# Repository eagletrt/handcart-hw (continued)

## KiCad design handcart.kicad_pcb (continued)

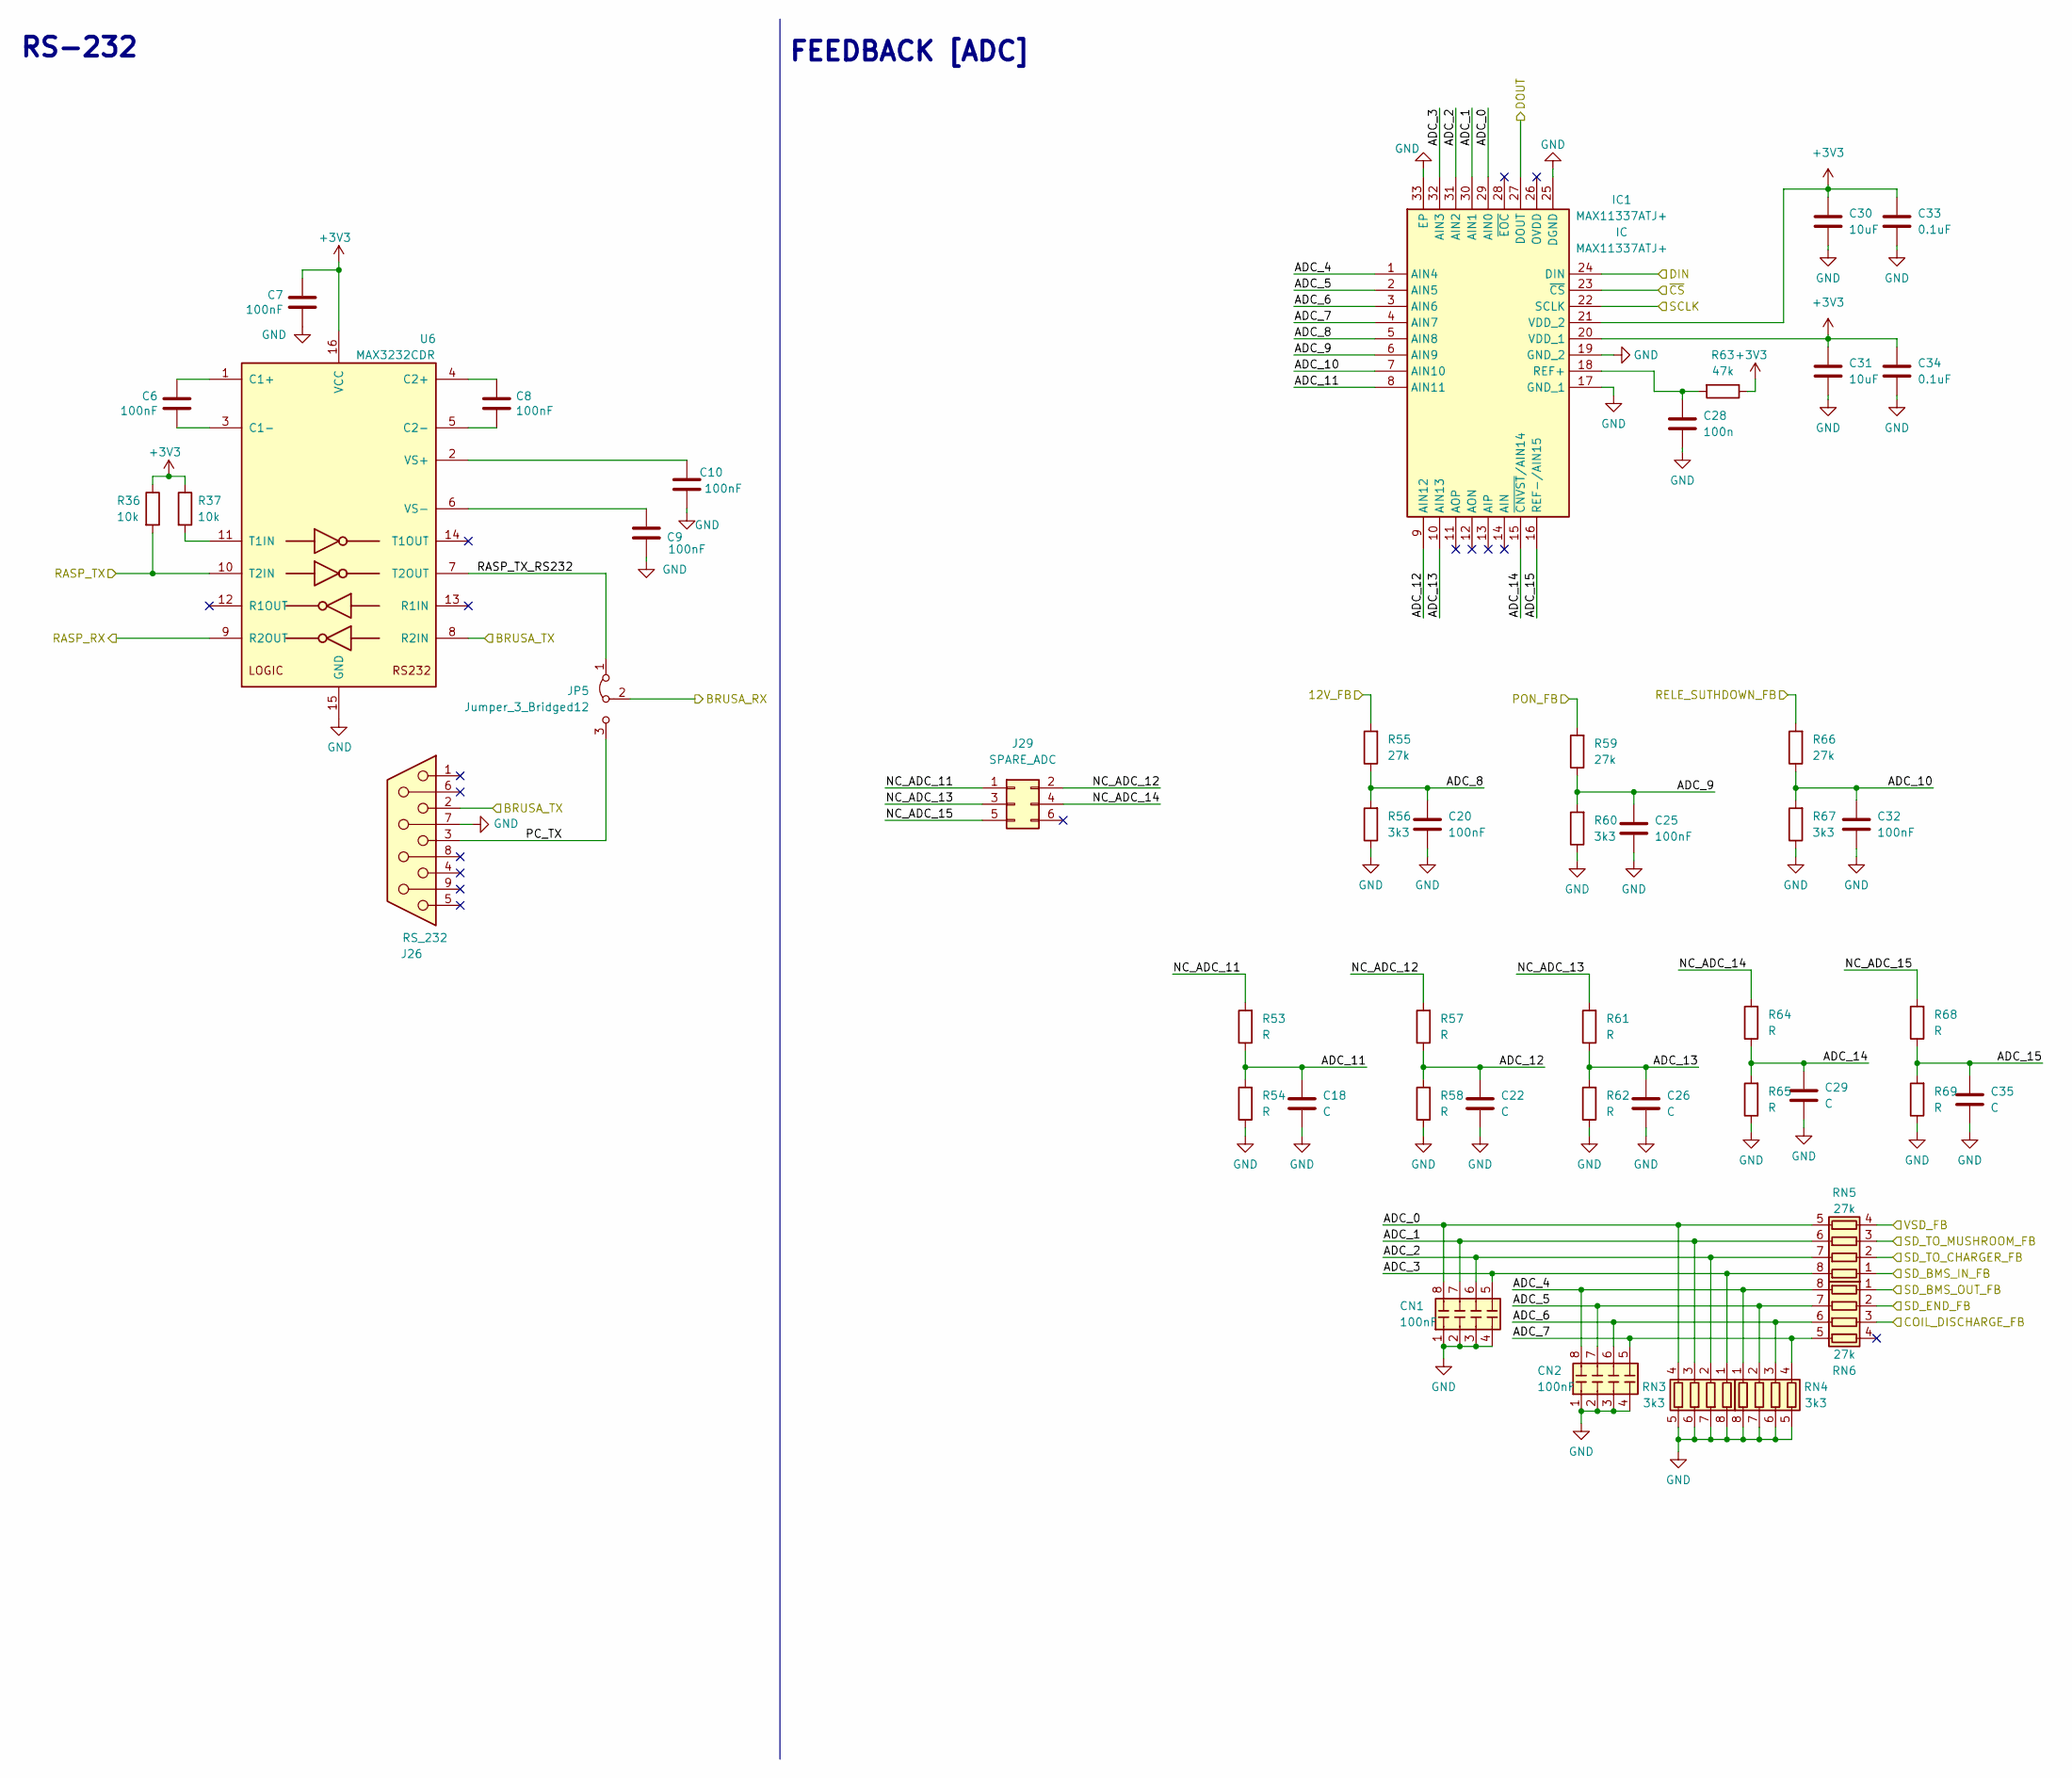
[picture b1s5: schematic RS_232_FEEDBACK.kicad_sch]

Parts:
C6, C7, C8, C9, C10, C20, C25, C32: 100nF; R_0603_1608Metric
C18, C22, C26, C29, C35: C; R_0805_2012Metric
C28: 100n; R_0603_1608Metric
C30, C31: 10uF; R_0603_1608Metric
C33, C34: 0.1uF; R_0603_1608Metric
CN1, CN2: 100nF; R_Array_Concave_4x0603; Mouser 581-W3A4YC104KAT2A
IC1: MAX11337ATJ+; QFN50P500X500X80-33N; Mouser Part Number 700-MAX11337ATJ+
J26: RS_232; DSUB-9_Female_Horizontal_P2.77x2.84mm_EdgePinOffset7.70mm_H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
J29: SPARE_ADC; Molex_Micro-Fit_3.0_43045-0612_2x03_P3.00mm_Vertical
JP5: Jumper_3_Bridged12; PinHeader_1x03_P2.54mm_Vertical
R36, R37: 10k; R_0603_1608Metric
R53, R54, R57, R58, R61, R62, R64, R65, R68, R69: R; R_0805_2012Metric
R55, R59, R66: 27k; R_0603_1608Metric
R56, R60, R67: 3k3; R_0603_1608Metric
R63: 47k; R_0603_1608Metric
RN3, RN4: 3k3; R_Array_Convex_4x0603
RN5, RN6: 27k; R_Array_Convex_4x0603
U6: MAX3232CDR; SOIC-16_3.9x9.9mm_P1.27mm

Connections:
+3V3: C7.1, C30.1, C31.1, C33.1, C34.1, IC1.20 (VDD_1), IC1.21 (VDD_2), R36.1, R37.1, R63.1, U6.16 (VCC); also elsewhere on the board
+12V: R55.2; also elsewhere on the board
/BRUSA_RX: JP5.2 (C); also elsewhere on the board
/BRUSA_TX: J26.2, U6.8 (R2IN); also elsewhere on the board
/PON: R59.2; also elsewhere on the board
/RS_232+FEEDBACK/ADC_0: CN1.8 (R1.2), IC1.29 (AIN0), RN3.4 (R4.1), RN5.5 (R4.2)
/RS_232+FEEDBACK/ADC_1: CN1.7 (R2.2), IC1.30 (AIN1), RN3.3 (R3.1), RN5.6 (R3.2)
/RS_232+FEEDBACK/ADC_2: CN1.6 (R3.2), IC1.31 (AIN2), RN3.2 (R2.1), RN5.7 (R2.2)
/RS_232+FEEDBACK/ADC_3: CN1.5 (R4.2), IC1.32 (AIN3), RN3.1 (R1.1), RN5.8 (R1.2)
/RS_232+FEEDBACK/ADC_4: CN2.8 (R1.2), IC1.1 (AIN4), RN4.1 (R1.1), RN6.8 (R1.2)
/RS_232+FEEDBACK/ADC_5: CN2.7 (R2.2), IC1.2 (AIN5), RN4.2 (R2.1), RN6.7 (R2.2)
/RS_232+FEEDBACK/ADC_6: CN2.6 (R3.2), IC1.3 (AIN6), RN4.3 (R3.1), RN6.6 (R3.2)
/RS_232+FEEDBACK/ADC_7: CN2.5 (R4.2), IC1.4 (AIN7), RN4.4 (R4.1), RN6.5 (R4.2)
/RS_232+FEEDBACK/ADC_8: C20.1, IC1.5 (AIN8), R55.1, R56.2
/RS_232+FEEDBACK/ADC_9: C25.1, IC1.6 (AIN9), R59.1, R60.2
/RS_232+FEEDBACK/ADC_10: C32.1, IC1.7 (AIN10), R66.1, R67.2
/RS_232+FEEDBACK/ADC_11: C18.1, IC1.8 (AIN11), R53.1, R54.2
/RS_232+FEEDBACK/ADC_12: C22.1, IC1.9 (AIN12), R57.1, R58.2
/RS_232+FEEDBACK/ADC_13: C26.1, IC1.10 (AIN13), R61.1, R62.2
/RS_232+FEEDBACK/ADC_14: C29.1, IC1.15 (~CNVST/AIN14), R64.1, R65.2
/RS_232+FEEDBACK/ADC_15: C35.1, IC1.16 (REF-/AIN15), R68.1, R69.2
/RS_232+FEEDBACK/COIL_DISCHARGE_FB: RN6.3 (R3.1); also elsewhere on the board
/RS_232+FEEDBACK/NC_ADC_11: J29.1, R53.2
/RS_232+FEEDBACK/NC_ADC_12: J29.2, R57.2
/RS_232+FEEDBACK/NC_ADC_13: J29.3, R61.2
/RS_232+FEEDBACK/NC_ADC_14: J29.4, R64.2
/RS_232+FEEDBACK/NC_ADC_15: J29.5, R68.2
/RS_232+FEEDBACK/PC_TX: J26.3, JP5.3 (B)
/RS_232+FEEDBACK/RASP_RX: U6.9 (R2OUT); also elsewhere on the board
/RS_232+FEEDBACK/RASP_TX: R36.2, U6.10 (T2IN); also elsewhere on the board
/RS_232+FEEDBACK/RASP_TX_RS232: JP5.1 (A), U6.7 (T2OUT)
/RS_232+FEEDBACK/RELE_SUTHDOWN_FB: R66.2; also elsewhere on the board
/RS_232+FEEDBACK/~CS: IC1.23 (~CS); also elsewhere on the board
/Raspberry/RASP_CLK: IC1.22 (SCLK); also elsewhere on the board
/Raspberry/RASP_MISO: IC1.27 (DOUT); also elsewhere on the board
/Raspberry/RASP_MOSI: IC1.24 (DIN); also elsewhere on the board
/SD_BMS_IN: RN5.1 (R1.1); also elsewhere on the board
/SD_BMS_OUT: RN6.1 (R1.1); also elsewhere on the board
/SD_END: RN6.2 (R2.1); also elsewhere on the board
/SD_TO_CHARGER: RN5.2 (R2.1); also elsewhere on the board
/SD_TO_MUSHROOM: RN5.3 (R3.1); also elsewhere on the board
GND: C7.2, C9.2, C10.2, C18.2, C20.2, C22.2, C25.2, C26.2, C28.2, C29.2, C30.2, C31.2, C32.2, C33.2, C34.2, C35.2, CN1.1 (R1.1), CN1.2 (R2.1), CN1.3 (R3.1), CN1.4 (R4.1), CN2.1 (R1.1), CN2.2 (R2.1), CN2.3 (R3.1), CN2.4 (R4.1), IC1.17 (GND_1), IC1.19 (GND_2), IC1.25 (DGND), IC1.33 (EP), J26.7, R54.1, R56.1, R58.1, R60.1, R62.1, R65.1, R67.1, R69.1, RN3.5 (R4.2), RN3.6 (R3.2), RN3.7 (R2.2), RN3.8 (R1.2), RN4.5 (R4.2), RN4.6 (R3.2), RN4.7 (R2.2), RN4.8 (R1.2), U6.15 (GND); also elsewhere on the board
unnamed: C6.1, U6.1 (C1+)
unnamed: C6.2, U6.3 (C1-)
unnamed: C8.1, U6.4 (C2+)
unnamed: C8.2, U6.5 (C2-)
unnamed: C9.1, U6.6 (VS-)
unnamed: C10.1, U6.2 (VS+)
unnamed: C28.1, IC1.18 (REF+), R63.2
unnamed: R37.2, U6.11 (T1IN)
VCC: RN5.4 (R4.1); also elsewhere on the board

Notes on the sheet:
RS-232
FEEDBACK [ADC]

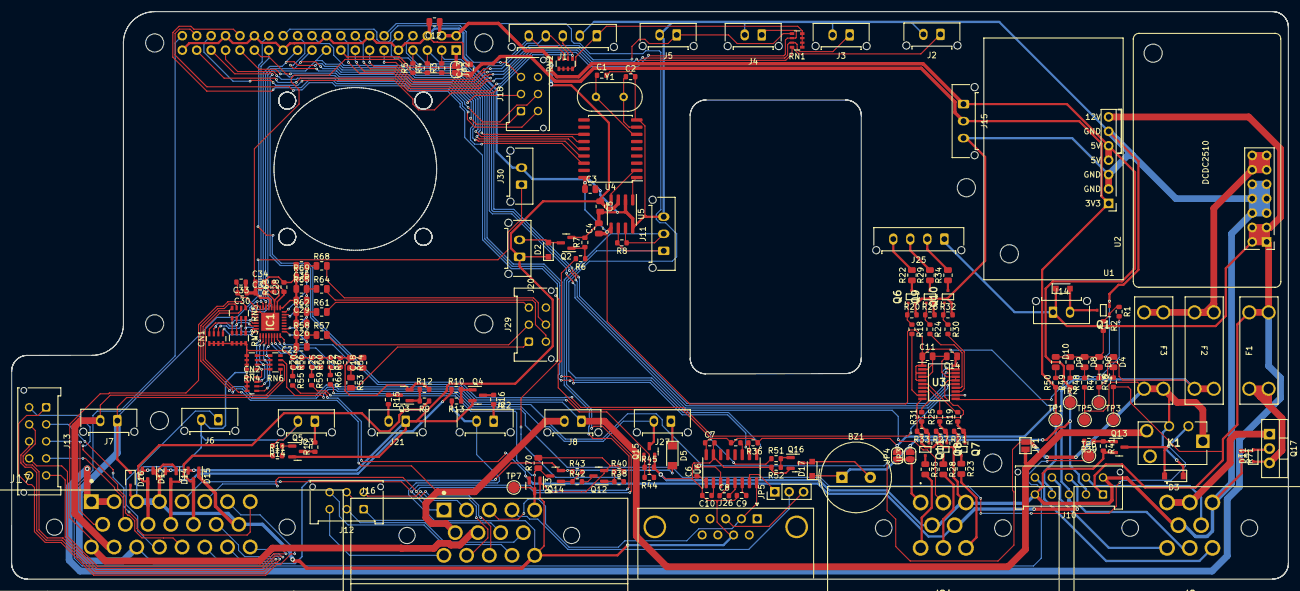
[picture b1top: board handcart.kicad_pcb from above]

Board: 2 copper layers, 225.0 x 100.0 mm, 193 parts (1 on the bottom side), 163 nets.

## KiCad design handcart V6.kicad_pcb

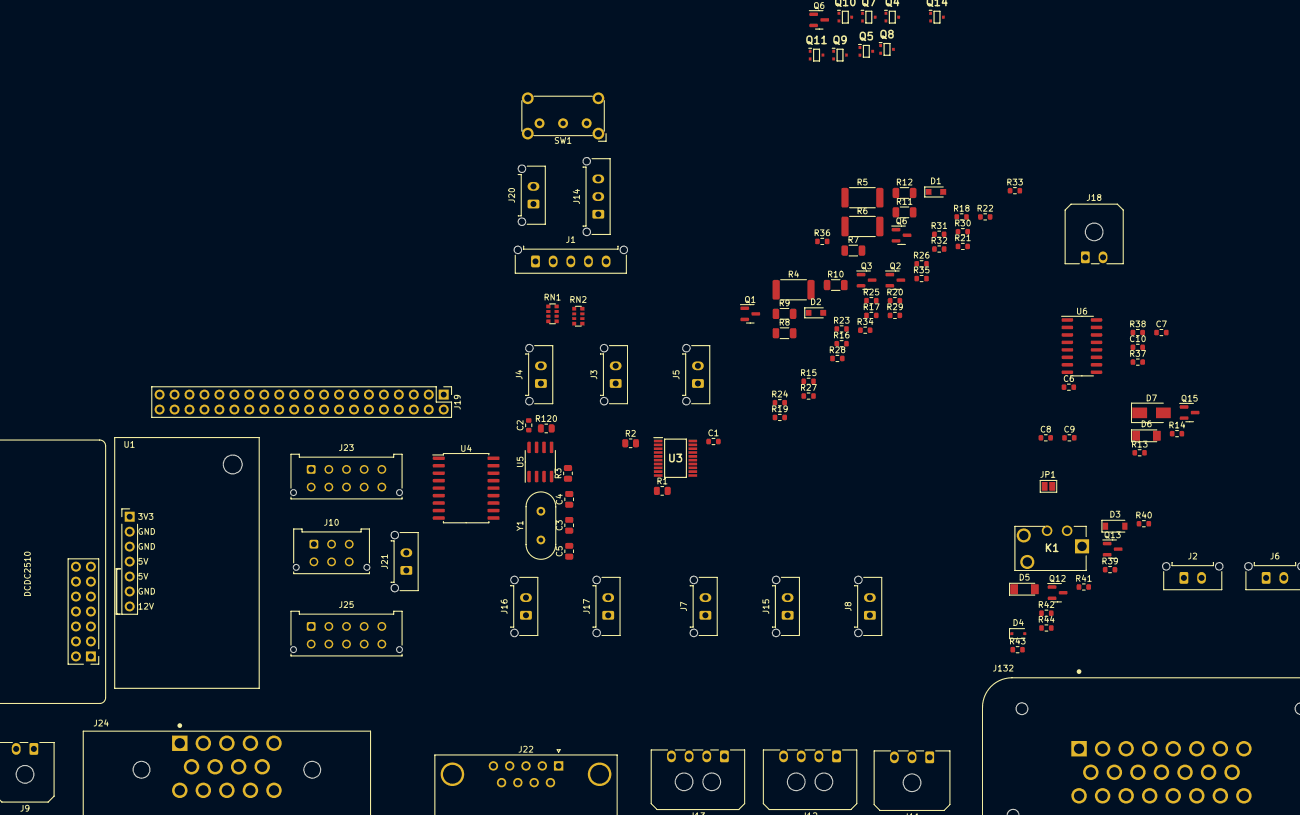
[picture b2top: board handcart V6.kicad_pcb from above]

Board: 2 copper layers, 116 parts (0 on the bottom side), 121 nets, no tracks yet.

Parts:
C1, C2: 18pF; R_0603_1608Metric
C3, C4, C5: 100nF; R_0805_2012Metric
C6, C7, C8, C9, C10: 100nF; R_0603_1608Metric
D1, D2: 1N4148W; D_SOD-323_HandSoldering
D3: 1N4148W; D_SOD-123
D4: DDZ13ASF 13V; D_SOD-323F
D5, D6: RGL34B; D_MiniMELF
D7: SMAJ40CA; D_SMA
J1: Conn_01x05; Molex_Micro-Fit_3.0_43650-0515_1x05_P3.00mm_Vertical
J2, J3, J4, J5, J6, J7, J8, J15, J16, J17, J20, J21: Conn_01x02; Molex_Micro-Fit_3.0_43650-0215_1x02_P3.00mm_Vertical
J9, J18: Conn_01x02; Molex_Micro-Fit_3.0_43650-0200_1x02_P3.00mm_Horizontal
J10: Conn_02x03_Odd_Even; Molex_Micro-Fit_3.0_43045-0612_2x03_P3.00mm_Vertical
J11: Conn_01x03; Molex_Micro-Fit_3.0_43650-0300_1x03_P3.00mm_Horizontal
J12, J13: Conn_01x04; Molex_Micro-Fit_3.0_43650-0400_1x04_P3.00mm_Horizontal
J14: Conn_01x03; Molex_Micro-Fit_3.0_43650-0315_1x03_P3.00mm_Vertical
J19: Raspberry_Pi_2_3; raspberrypi_hat_template
J22: DB9_Female_DCE; DSUB-9_Female_Horizontal_P2.77x2.84mm_EdgePinOffset7.70mm_H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
J23: Conn_02x05; Molex_Micro-Fit_3.0_43045-1012_2x05_P3.00mm_Vertical
J24: TE_AmpSeal_14_776273-1; TE_776266-4
J25: Conn_02x06_Top_Bottom; Molex_Micro-Fit_3.0_43045-1012_2x05_P3.00mm_Vertical
J132: TE_Ampseal_23; TE_1-776228-4
JP1: SolderJumper_2_Open; SolderJumper-2_P1.3mm_Open_Pad1.0x1.5mm
K1: EX12U1S
Q1, Q6, Q6#2, Q15: 2N7002NXAK; SOT-23
Q2, Q3, Q13: NTR5105PT1G; SOT-23
Q4, Q5, Q7, Q8, Q9, Q10, Q11, Q14: SSM3K361TU,LF; SOTFL65P210X75-3N
Q12: 2N7002NXAKR; SOT-23
R1, R2, R3: 10k; R_0805_2012Metric
R4, R5, R6: 120R; R_2512_6332Metric
R7, R8, R9, R10, R11, R12: R; R_1206_3216Metric
R13: 33; R_0603_1608Metric
R14, R37, R38: 10k; R_0603_1608Metric
R15, R16, R17, R21, R23, R25, R27, R29, R31, R33, R35, R39, R41, R43: 22; R_0603_1608Metric
R18, R19, R20, R22, R24, R26, R28, R30, R32, R34, R36, R40, R42, R44: 330k; R_0603_1608Metric
R120: R; R_0805_2012Metric
RN1, RN2: 100k; R_Array_Convex_4x0612
SW1: SW_SPDT; SW_E-Switch_EG1224_SPDT_Angled
U1: Tex_DCDC_v2; Tex_DCDC_v2_horizontal
U2: DCDC2510; DCDC2510_Horizontal
U3: PCA9634PW,118; SOP65P640X110-20N
U4: MCP2515-xSO; SOIC-18W_7.5x11.6mm_P1.27mm
U5: MCP2562-E-SN; SOIC-8_3.9x4.9mm_P1.27mm
U6: MAX3232CDR; SOIC-16_3.9x9.9mm_P1.27mm
Y1: 16MHz; Crystal_HC49-4H_Vertical

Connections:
+3.3V: C7.1, J1.1, R37.1, R38.1, RN1.1 (R1.1), RN1.2 (R2.1), RN1.3 (R3.1), RN1.4 (R4.1), RN2.1 (R1.1), RN2.2 (R2.1), RN2.3 (R3.1), RN2.4 (R4.1), U6.16 (VCC)
+3V3: C3.1, C4.1, J14.2, J19.1 (3V3), J19.17 (3V3), R1.1, R2.1, R3.1, U1.1 (3V3), U3.1 (A0), U3.3 (A2), U3.5 (A4), U3.20 (VDD), U4.18 (VDD), U5.5 (Vio)
+5V: C5.1, D1.1 (K), J14.1, J15.1, J19.2 (5V), J19.4 (5V), J20.1, Q2.2 (S), Q3.2 (S), U1.4 (5V), U1.5 (5V), U5.3 (VDD)
+12V: D3.1 (K), J12.1, J13.1, J24.13, J132.1, K1.3, U2.11 (VDD), U2.12 (VDD), U2.13 (VDD), U2.14 (VDD)
+24V: D2.1 (K), J8.1, J9.1, J21.1, J24.11, J132.2, U1.7 (VIN), U2.1 (VCC), U2.2 (VCC), U2.3 (VCC), U2.4 (VCC)
/BMS_LED: J132.13, R17.1
/BRUSA_RX: J24.4, SW1.2 (B)
/BRUSA_TX: J22.2, J24.3, U6.8 (R2IN)
/BUT_0: J1.5, J19.15 (GPIO22), RN1.5 (R4.2)
/BUT_1: J2.1, J19.16 (GPIO23), RN1.6 (R3.2)
/BUT_2: J3.1, J19.18 (GPIO24), RN1.7 (R2.2)
/BUT_3: J4.1, J19.37 (GPIO26), RN1.8 (R1.2)
/BUT_4: J5.1, J19.13 (GPIO27), RN2.5 (R4.2)
/CAN_N: J11.2, J24.2, J132.6, R120.2, U5.6 (CANL)
/CAN_P: J11.1, J24.1, J132.5, R120.1, U5.7 (CANH)
/DISCHARGE_N: D7.1 (A1), J18.2, Q15.3 (D)
/DISCHARGE_P: D6.1 (K), D7.2 (A2), J18.1
/GREEN_TS_OFF: J15.2, R4.2
/IMD_LED: J132.12, R16.1
/NC_BMS_1: J23.1, J132.7
/NC_BMS_2: J23.2, J132.8
/NC_BMS_3: J23.3, J132.9
/NC_BMS_4: J23.4, J132.10
/NC_BMS_5: J23.5, J132.14
/NC_BMS_6: J23.6, J132.20
/NC_BMS_7: J23.7, J132.21
/NC_BMS_8: J23.8, J132.22
/NC_BMS_9: J23.9, J132.23
/NC_CRG_1: J10.1, J24.8
/NC_CRG_2: J10.2, J24.9
/NC_CRG_3: J10.3, J24.10
/Output/ADD_FAN_PWM: R35.2, U3.11 (LED4)
/Output/RASPY_FAN_PWM: R33.2, U3.12 (LED5)
/Output/RASPY_STRIP1_B: R31.2, U3.8 (LED2)
/Output/RASPY_STRIP1_G: R29.2, U3.7 (LED1)
/Output/RASPY_STRIP1_R: R27.2, U3.6 (LED0)
/Output/RASPY_TSAL_B: R25.2, U3.13 (LED6)
/Output/RASPY_TSAL_G: R23.2, U3.14 (LED7)
/Output/RASPY_TSAL_R: R21.2, U3.9 (LED3)
/PON: J24.5, Q13.3 (D)
/RASP_PON_CHARGER: J19.35 (GPIO19/MISO1), R13.2
/RASP_PON_CONTROL: J19.40 (GPIO21/SCLK1), R43.2
/RASP_SD_CONTROL: J19.38 (GPIO20/MOSI1), R39.2
/RED_BMS_FAULT: J16.1, R5.1
/RED_IMD_FAULT: J17.1, R6.1
/RESET_BUTTON: J6.1, J132.19
/ROT_A: J1.3, J19.36 (GPIO16), RN2.6 (R3.2)
/ROT_B: J1.4, J19.11 (GPIO17), RN2.7 (R2.2)
/RS_232/PC_TX: J22.3, SW1.3 (C)
/RS_232/RASP_RX: J19.10 (GPIO15/RXD), U6.9 (R2OUT)
/RS_232/RASP_TX: J19.8 (GPIO14/TXD), R37.2, U6.10 (T2IN)
/RS_232/RASP_TX_RS232: SW1.1 (A), U6.7 (T2OUT)
/Raspberry/CAN_~INT: J19.22 (GPIO25), U4.12 (~INT)
/Raspberry/NC_RASP_1: J19.29 (GCLK1/GPIO5), J25.1
/Raspberry/NC_RASP_2: J19.31 (GCLK2/GPIO6), J25.2
/Raspberry/NC_RASP_3: J19.26 (~CE1/GPIO7), J25.3
/Raspberry/NC_RASP_4: J19.32 (PWM0/GPIO12), J25.4
/Raspberry/NC_RASP_5: J19.33 (PWM1/GPIO13), J25.5
/Raspberry/NC_RASP_6: J19.27 (ID_SD/GPIO0), J25.6
/Raspberry/NC_RASP_7: J19.28 (ID_SC/GPIO1), J25.7
/Raspberry/NC_RASP_8: J19.12 (GPIO18/PWM0), J25.8
/Raspberry/RASP_CLK: J19.23 (SCLK0/GPIO11), U4.13 (SCK)
/Raspberry/RASP_MISO: J19.21 (MISO0/GPIO9), U4.15 (SO)
/Raspberry/RASP_MOSI: J19.19 (MOSI0/GPIO10), U4.14 (SI)
/Raspberry/RASP_~CS: J19.24 (~CE0/GPIO8), U4.16 (~CS)
/Raspberry/SCL: J19.5 (SCL/GPIO3), R2.2, U3.18 (SCL)
/Raspberry/SDA: J19.3 (SDA/GPIO2), R1.2, U3.19 (SDA)
/Raspberry/~OE: J19.7 (GCLK0/GPIO4), R3.2, U3.15 (~OE)
/SD_BMS_IN: J24.7, J132.16
/SD_BMS_OUT: D6.2 (A), J7.2, J132.17
/SD_END: D4.1 (K), D5.2 (A), J7.1, Q13.2 (S), R42.1
/SD_END_HV: D5.1 (K), J132.18
/SD_FROM_MUSHROOM: J8.2, JP1.1 (A), K1.1
/SD_TO_CHARGER: J24.6, JP1.2 (B), K1.4
/STRIP1_B: J13.4, R12.2
/STRIP1_G: J13.3, R11.2
/STRIP1_R: J13.2, R10.2
/TSAL: J132.11, R15.1
/TSAL_B: J12.4, R9.2
/TSAL_G: J12.3, R8.2
/TSAL_R: J12.2, R7.2
GND: C1.2, C2.2, C3.2, C4.2, C5.2, C7.2, C9.2, C10.2, D4.2 (A), J1.2, J2.2, J3.2, J4.2, J5.2, J6.2, J9.2, J11.3, J14.3, J16.2, J17.2, J19.6 (GND), J19.9 (GND), J19.14 (GND), J19.20 (GND), J19.25 (GND), J19.30 (GND), J19.34 (GND), J19.39 (GND), J22.7, J24.12, J24.14, J132.3, J132.4, J132.15, Q1.2 (S), Q4.2 (S), Q5.2 (S), Q6.2 (S), Q6#2.2 (S), Q7.2 (S), Q8.2 (S), Q9.2 (S), Q10.2 (S), Q11.2 (S), Q12.2 (S), Q14.2 (S), Q15.2 (S), R14.2, R18.2, R19.2, R20.2, R22.2, R24.2, R26.2, R28.2, R30.2, R32.2, R34.2, R36.2, R40.2, R44.2, U1.2 (GND), U1.3 (GND), U1.6 (GND), U2.5 (GND), U2.6 (GND), U2.7 (GND), U2.8 (GND), U2.9 (GND), U2.10 (GND), U3.2 (A1), U3.4 (A3), U3.10 (VSS), U3.16 (A5), U3.17 (A6), U4.9 (VSS), U5.2 (VSS), U5.8 (STBY), U6.15 (GND)
unnamed: C1.1, U4.7 (OSC2), Y1.1
unnamed: C2.1, U4.8 (OSC1), Y1.2
unnamed: C6.1, U6.1 (C1+)
unnamed: C6.2, U6.3 (C1-)
unnamed: C8.1, U6.4 (C2+)
unnamed: C8.2, U6.5 (C2-)
unnamed: C9.1, U6.6 (VS-)
unnamed: C10.1, U6.2 (VS+)
unnamed: D1.2 (A), J20.2, Q6.3 (D), Q6#2.3 (D)
unnamed: D2.2 (A), J21.2, Q9.3 (D)
unnamed: D3.2 (A), K1.2, Q14.3 (D)
unnamed: Q1.1 (G), R15.2, R18.1
unnamed: Q1.3 (D), R4.1
unnamed: Q2.1 (G), R16.2, R19.1
unnamed: Q2.3 (D), R5.2
unnamed: Q3.1 (G), R17.2, R20.1
unnamed: Q3.3 (D), R6.2
unnamed: Q7.3 (D), R9.1
unnamed: Q11.3 (D), R12.1
unnamed: Q12.1 (G), R39.1, R40.1
unnamed: Q12.3 (D), R41.2
unnamed: Q13.1 (G), R41.1, R42.2
unnamed: Q15.1 (G), R13.1, R14.1
unnamed: Q4.3 (D), R7.1
unnamed: Q5.3 (D), R8.1
unnamed: Q8.3 (D), R10.1
unnamed: Q10.3 (D), R11.1
unnamed: Q4.1 (G), R21.1, R22.1
unnamed: Q5.1 (G), R23.1, R24.1
unnamed: Q7.1 (G), R25.1, R26.1
unnamed: Q8.1 (G), R27.1, R28.1
unnamed: Q10.1 (G), R29.1, R30.1
unnamed: Q11.1 (G), R31.1, R32.1
unnamed: Q6#2.1 (G), R33.1, R34.1
unnamed: Q9.1 (G), R35.1, R36.1
unnamed: R38.2, U6.11 (T1IN)
unnamed: Q14.1 (G), R43.1, R44.1
unnamed: U4.1 (TXCAN), U5.1 (TXD)
unnamed: U4.2 (RXCAN), U5.4 (RXD)

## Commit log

2021-07-31 First revision, all seems ok
2021-07-31 added button labels on schematic
2021-08-03 added mounting holes
2021-08-04 added fan hole to pi
2021-08-04 All mounting holes to M3
2021-08-08 as printed v2
2021-11-11 added documentation and .step output
2021-11-12 changed relay, modified gitignore, did the output
2021-11-12 docs: remove broken symlink
2021-11-20 missing holes added
2021-12-01 renamed SD nets
2023-02-04 added handcart hardware/ wiring documentation
2023-02-04 added handcart hardware/ wiring documentation (#7)
2023-10-26 New version of the board. Added new features. For all of the changes refers to the documentation
2023-10-26 Changed mosfet, fixed all the datasheets, added 3D models
2023-11-02 Major changes after the schematic review. Refer to Github for all the changes
2023-11-16 modified schematic and started design pcb
2023-11-16 Fixed frequency of LPF, added reverse polarity protection
2023-11-22 First version of the pcb layout
2023-11-27 Second iteration of the board layout. Need to fix some traces
2023-12-03 Added connector, fixed traces, first version of silkscreen
2023-12-15 Fixed vias diameter, fixed width of the input trace to the DCDC, completed the front silkscreen and added the back silkscreen
2023-12-19 Fixed Schematic, fixed some traces. Still not finished
2023-12-21 Fixed traces, modified silkscreen
2023-12-21 Added information on silkscreen
2023-12-22 production candidate
    cleaned graphics
    aligned connectors
    exported fabrication files
